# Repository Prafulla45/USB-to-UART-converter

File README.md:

# USB to UART Converter

This repository contains a simple USB to UART converter PCB designed in KiCad. It is a practice project focused on learning schematic capture, PCB layout, routing, and 3D visualization.

The design uses a USB Type-C input and a CP2102N USB-to-UART bridge to expose serial signals on an external pin header. The board also includes supporting passive components, indicator LEDs, and the required USB power and signal connections.

## Project Overview

- USB Type-C connector for power and USB data
- CP2102N USB-to-UART bridge
- External UART header for serial access
- Compact PCB layout with routed traces and silkscreen labeling

## Files In This Project

- USB to UART converter.kicad_pro - KiCad project file
- USB to UART converter.kicad_sch - schematic
- USB to UART converter.kicad_pcb - PCB layout
- frontView.png - front 3D view of the board
- backView.png - back 3D view of the board
- routing.png - PCB routing view
- schematics.png - schematic screenshot

## Board Images

### Front View

### Back View

### Routing View

### Schematic

## Notes

This is a practice project, so it is intended for learning and experimentation rather than production use.
Hence some missing footprint library is ignored.

## Working With The Design

Open the project in KiCad to inspect the schematic, board layout, and 3D model. From there you can review the routing, modify the component placement, or export fabrication files if needed.

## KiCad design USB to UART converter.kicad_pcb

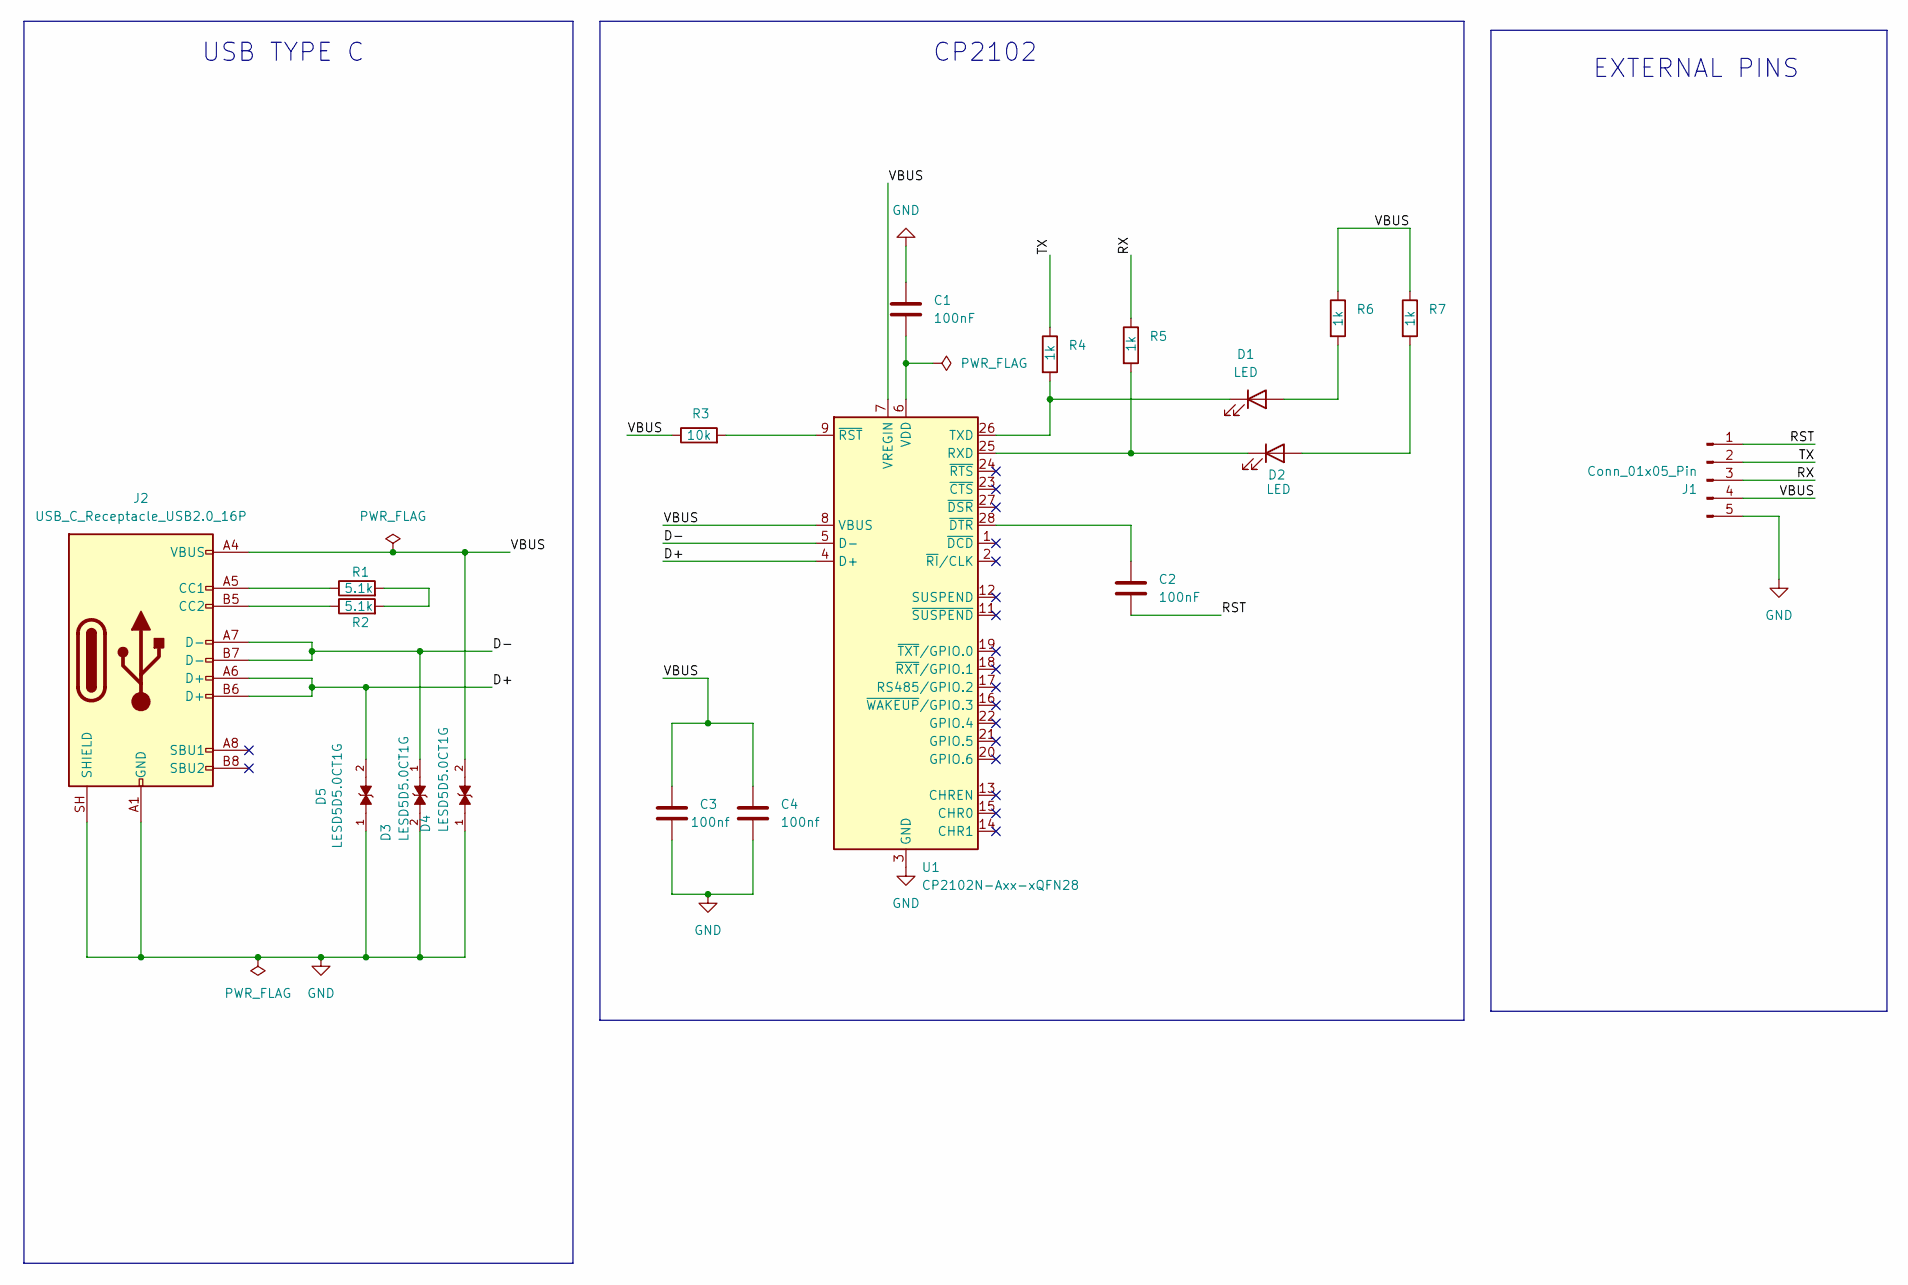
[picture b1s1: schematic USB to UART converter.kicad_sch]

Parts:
C1, C2: 100nF; C_0201_0603Metric
C3, C4: 100nf; C_0201_0603Metric
D1, D2: LED; LED_0201_0603Metric
D3, D4, D5: LESD5D5.0CT1G; TVS_LESD5D5.0CT1G; PARTREV O
J1: Conn_01x05_Pin; PinHeader_1x05_P2.54mm_Horizontal
J2: USB_C_Receptacle_USB2.0_16P; USB_C_Receptacle_HRO_TYPE-C-31-M-12
R1, R2: 5.1k; R_0201_0603Metric
R3: 10k; R_0201_0603Metric
R4, R5, R6, R7: 1k; R_0201_0603Metric
U1: CP2102N-Axx-xQFN28; QFN-28-1EP_5x5mm_P0.5mm_EP3.35x3.35mm

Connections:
/D+: D5.2, J2.A6 (D+), J2.B6 (D+), U1.4 (D+)
/D-: D3.1, J2.A7 (D-), J2.B7 (D-), U1.5 (D-)
/RST: C2.2, J1.1
/RX: J1.3, R5.1
/TX: J1.2, R4.1
/VBUS: C3.1, C4.1, D4.2, J1.4, J2.A4 (VBUS), J2.A9 (VBUS), J2.B4 (VBUS), J2.B9 (VBUS), R3.1, R6.1, R7.1, U1.7 (VREGIN), U1.8 (VBUS)
GND: C1.1, C3.2, C4.2, D3.2, D4.1, D5.1, J1.5, J2.A1 (GND), J2.A12 (GND), J2.B1 (GND), J2.B12 (GND), J2.SH (SHIELD), U1.3 (GND), U1.29 (GND)
unnamed: D1.2 (A), R6.2
unnamed: D1.1 (K), R4.2, U1.26 (TXD)
unnamed: D2.2 (A), R7.2
unnamed: D2.1 (K), R5.2, U1.25 (RXD)
unnamed: J2.A5 (CC1), R1.1
unnamed: J2.B5 (CC2), R2.1
unnamed: R1.2, R2.2
unnamed: C1.2, U1.6 (VDD)
unnamed: C2.1, U1.28 (~DTR)
unnamed: R3.2, U1.9 (~RST)

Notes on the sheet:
EXTERNAL PINS
USB TYPE C
CP2102

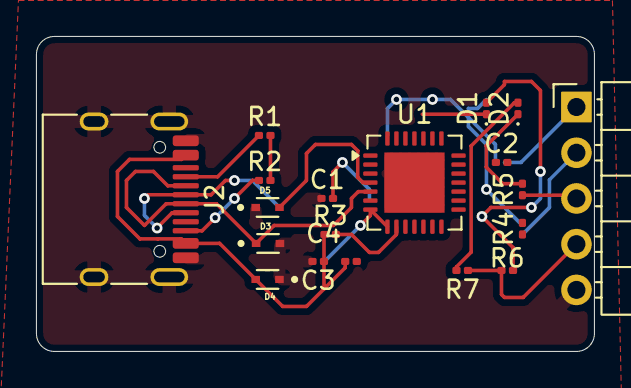
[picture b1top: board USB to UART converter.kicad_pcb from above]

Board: 2 copper layers, 31.0 x 17.5 mm, 19 parts (0 on the bottom side), 17 nets.

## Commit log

2026-04-09 Schematic design of USB to UART converter
2026-04-10 Updated schematic design
2026-04-10 Added gitignore
2026-04-10 Updated PCB and schematic design
2026-06-11 Updated readme file
